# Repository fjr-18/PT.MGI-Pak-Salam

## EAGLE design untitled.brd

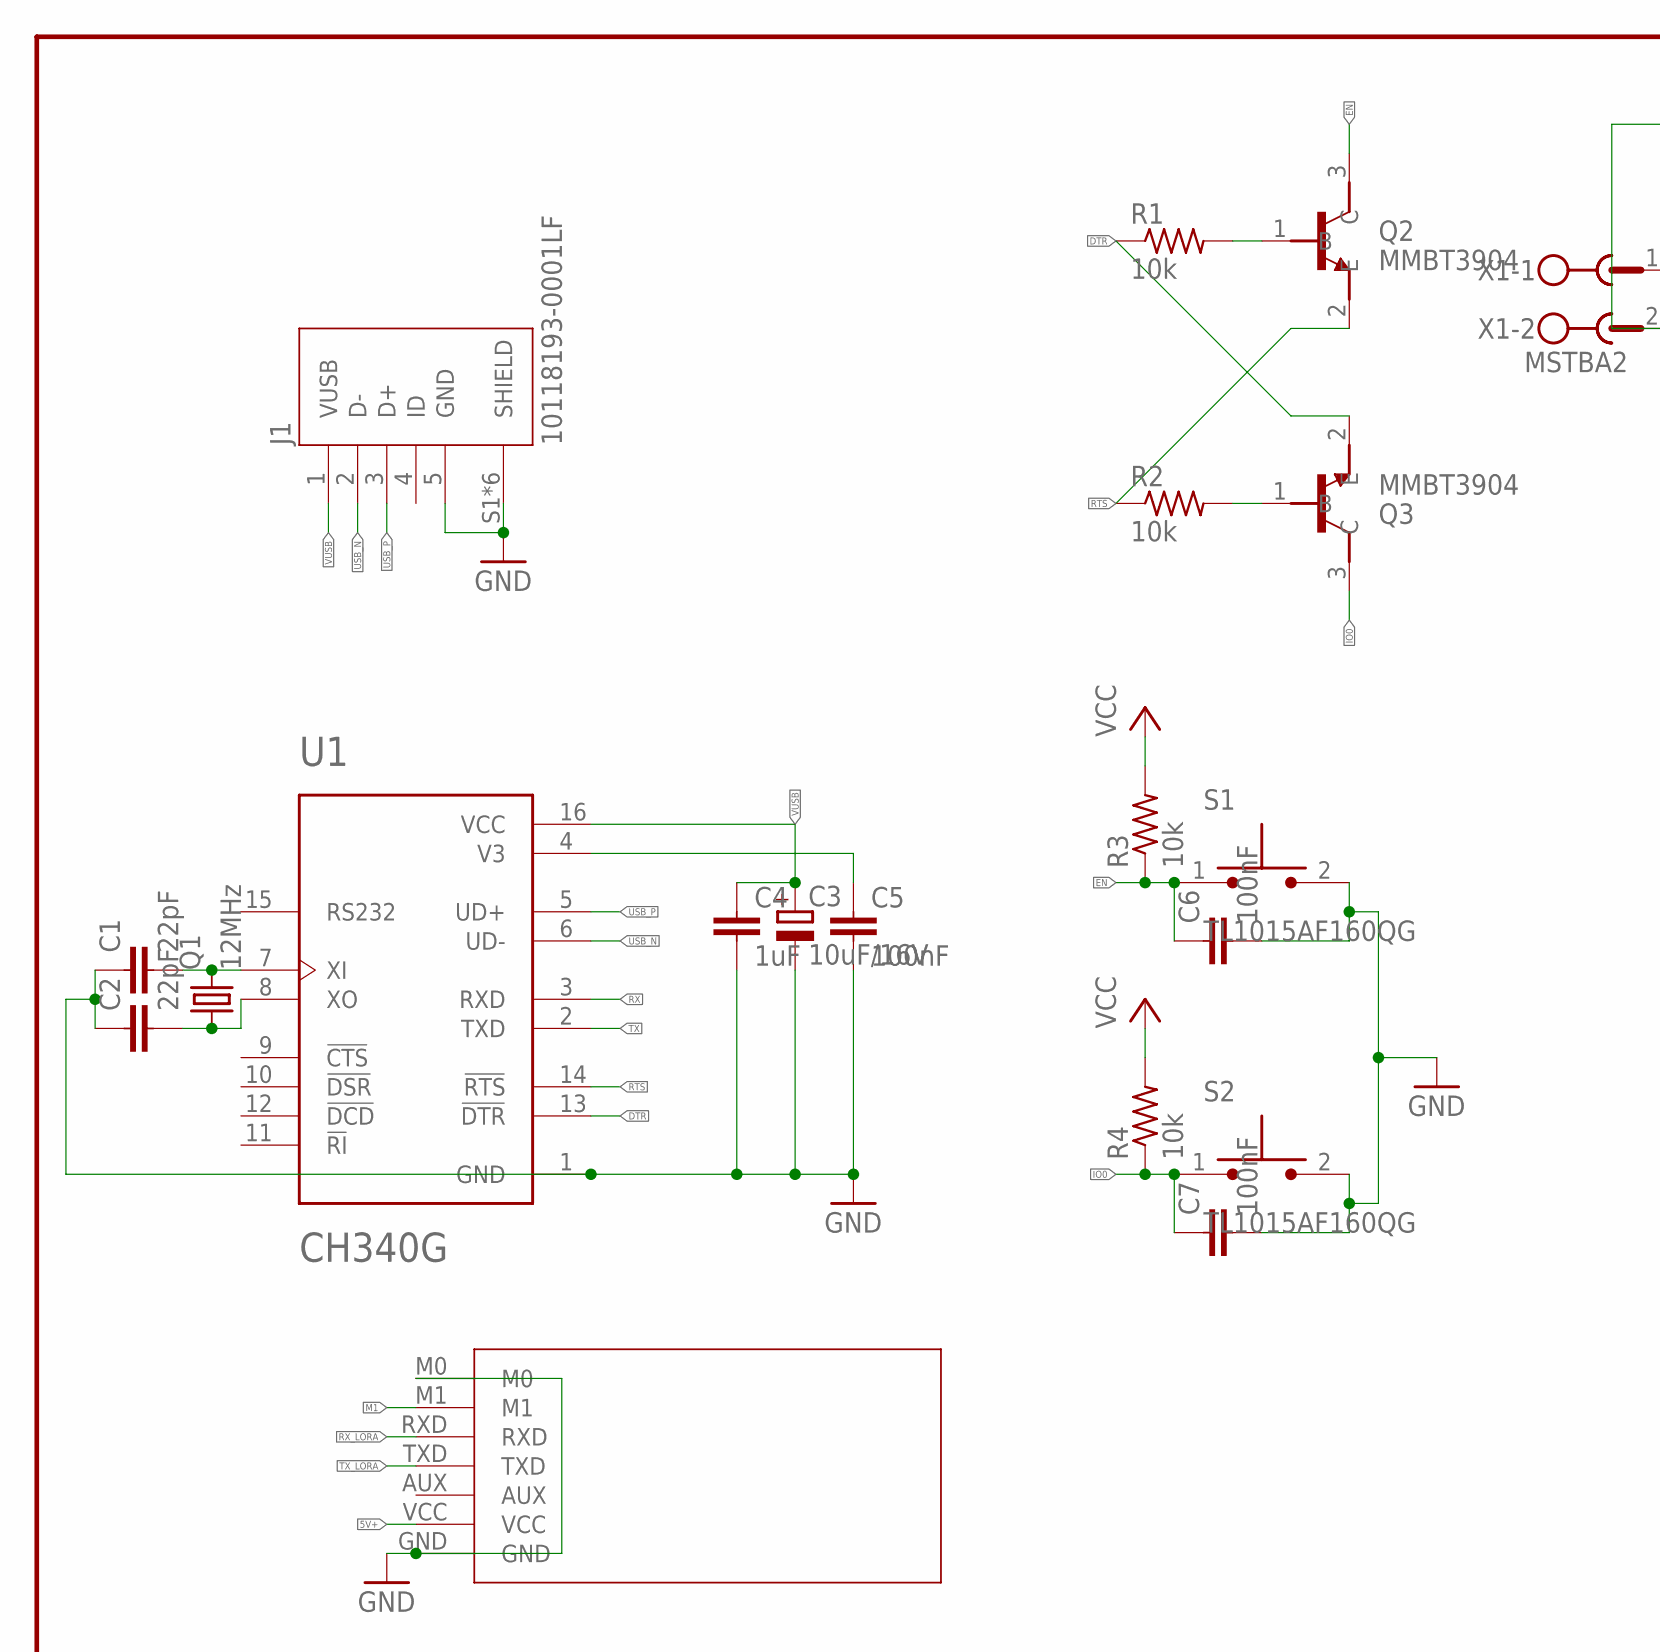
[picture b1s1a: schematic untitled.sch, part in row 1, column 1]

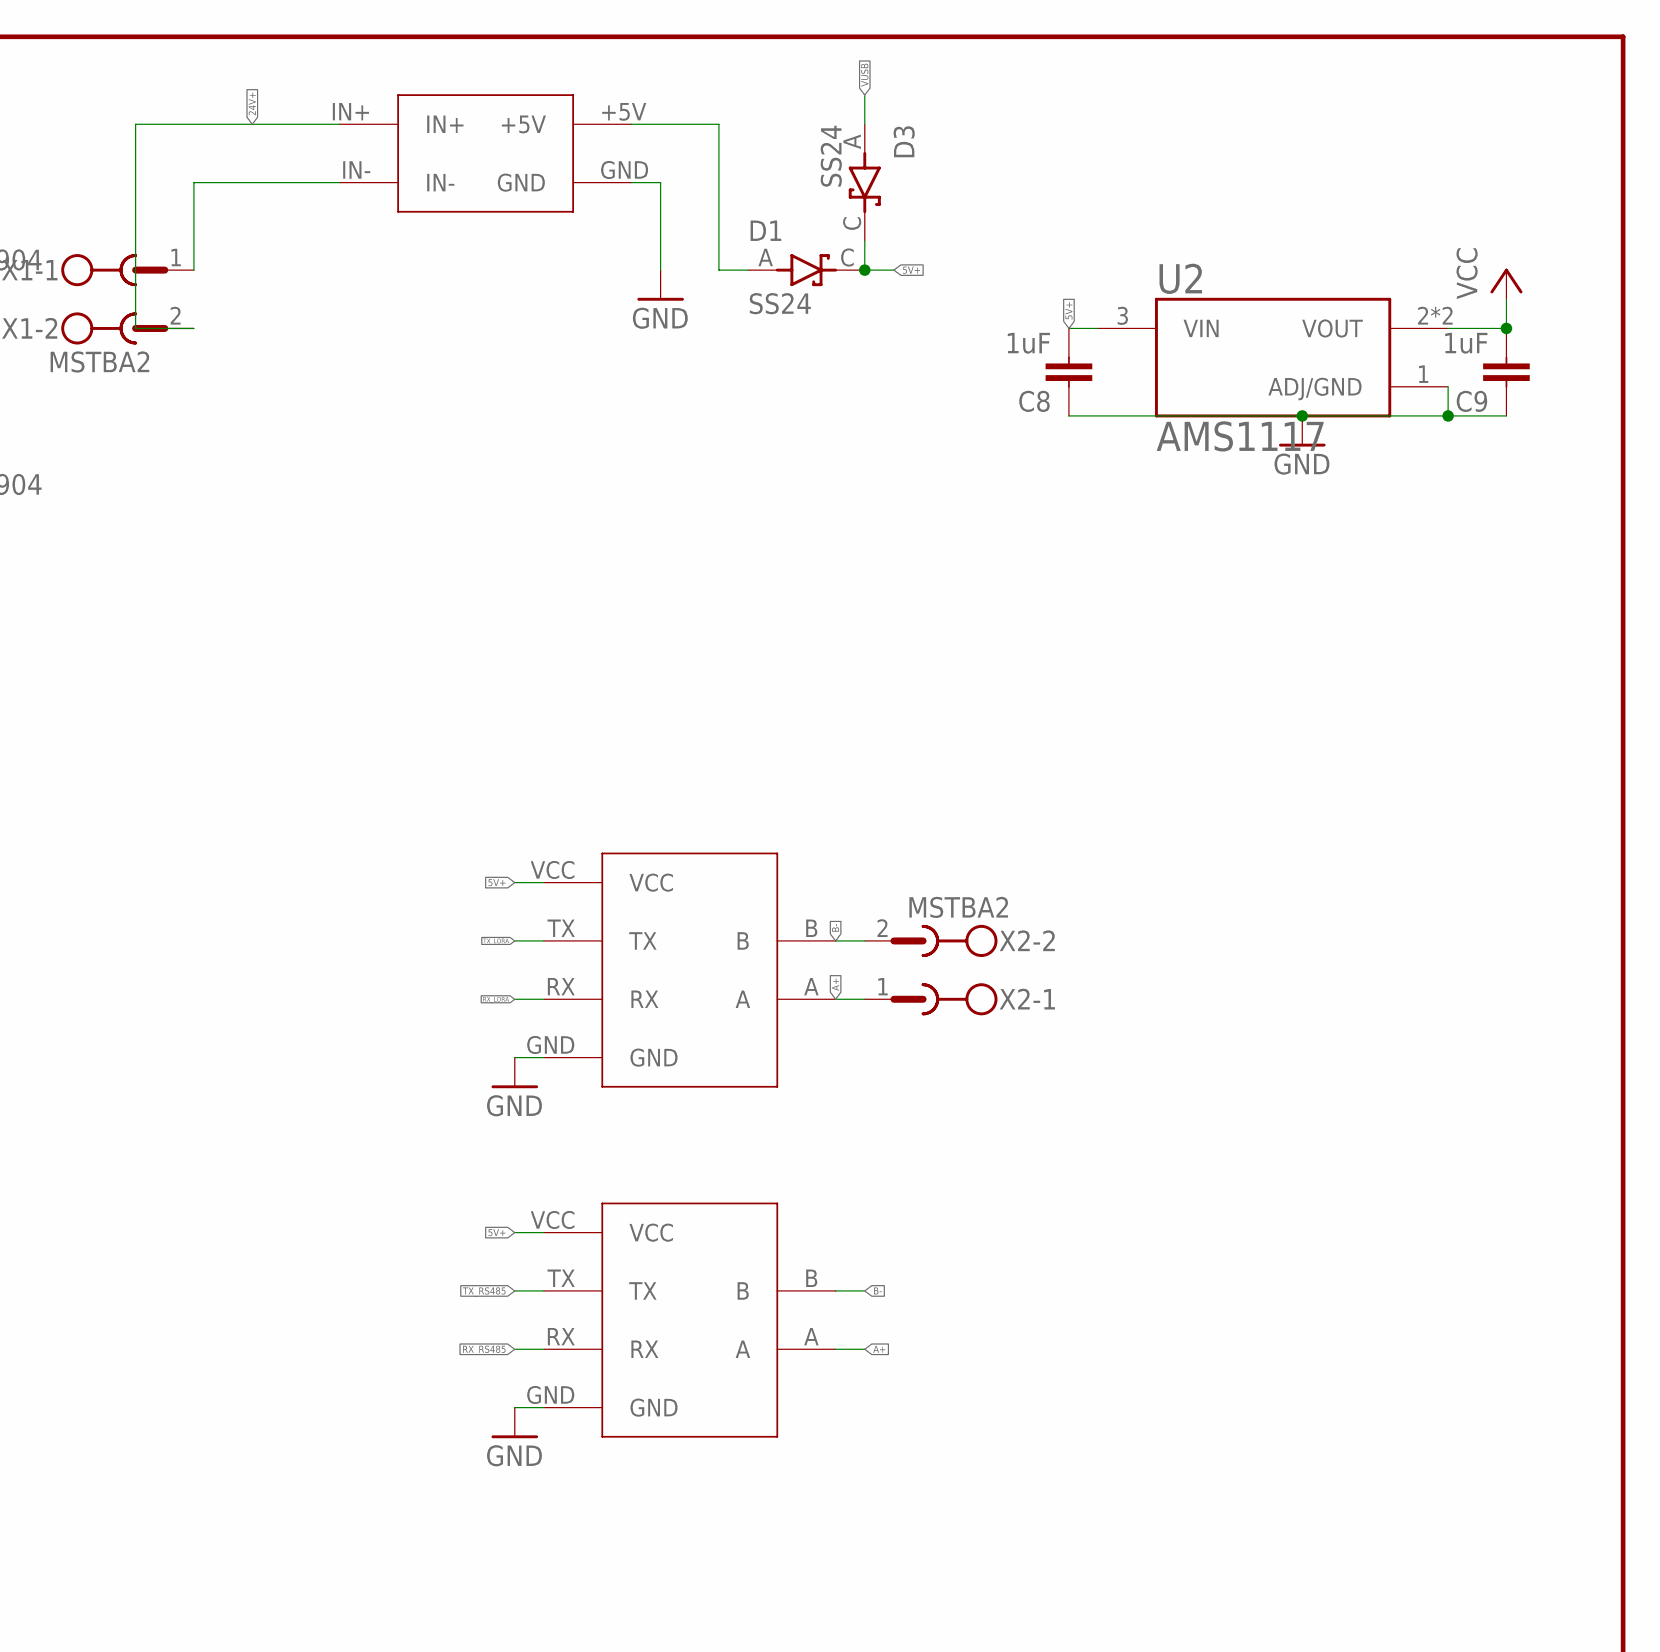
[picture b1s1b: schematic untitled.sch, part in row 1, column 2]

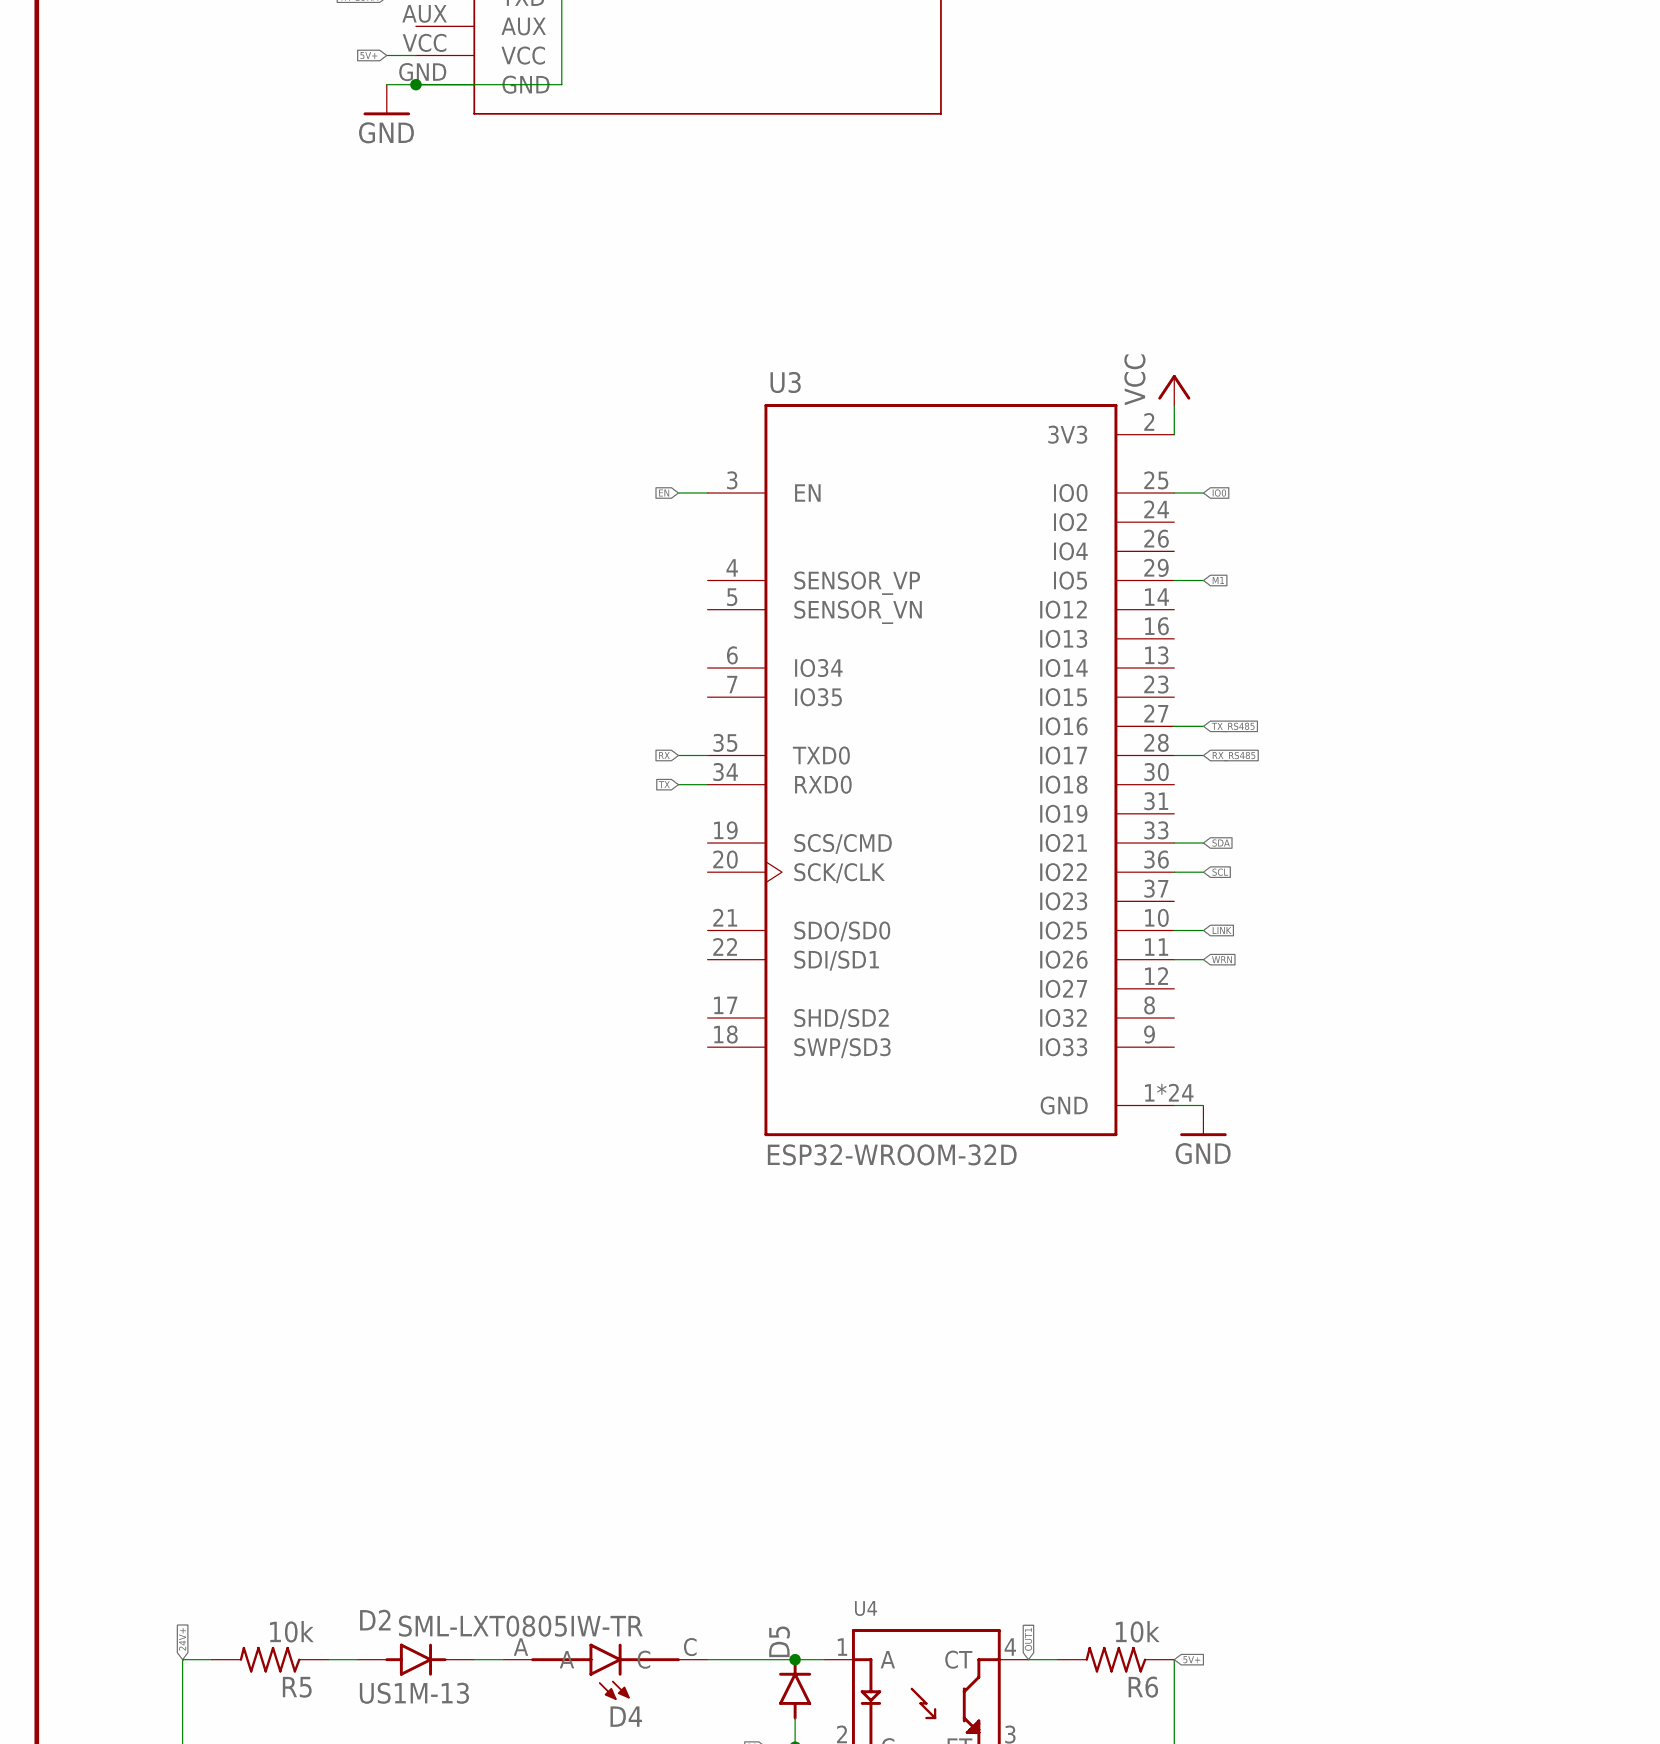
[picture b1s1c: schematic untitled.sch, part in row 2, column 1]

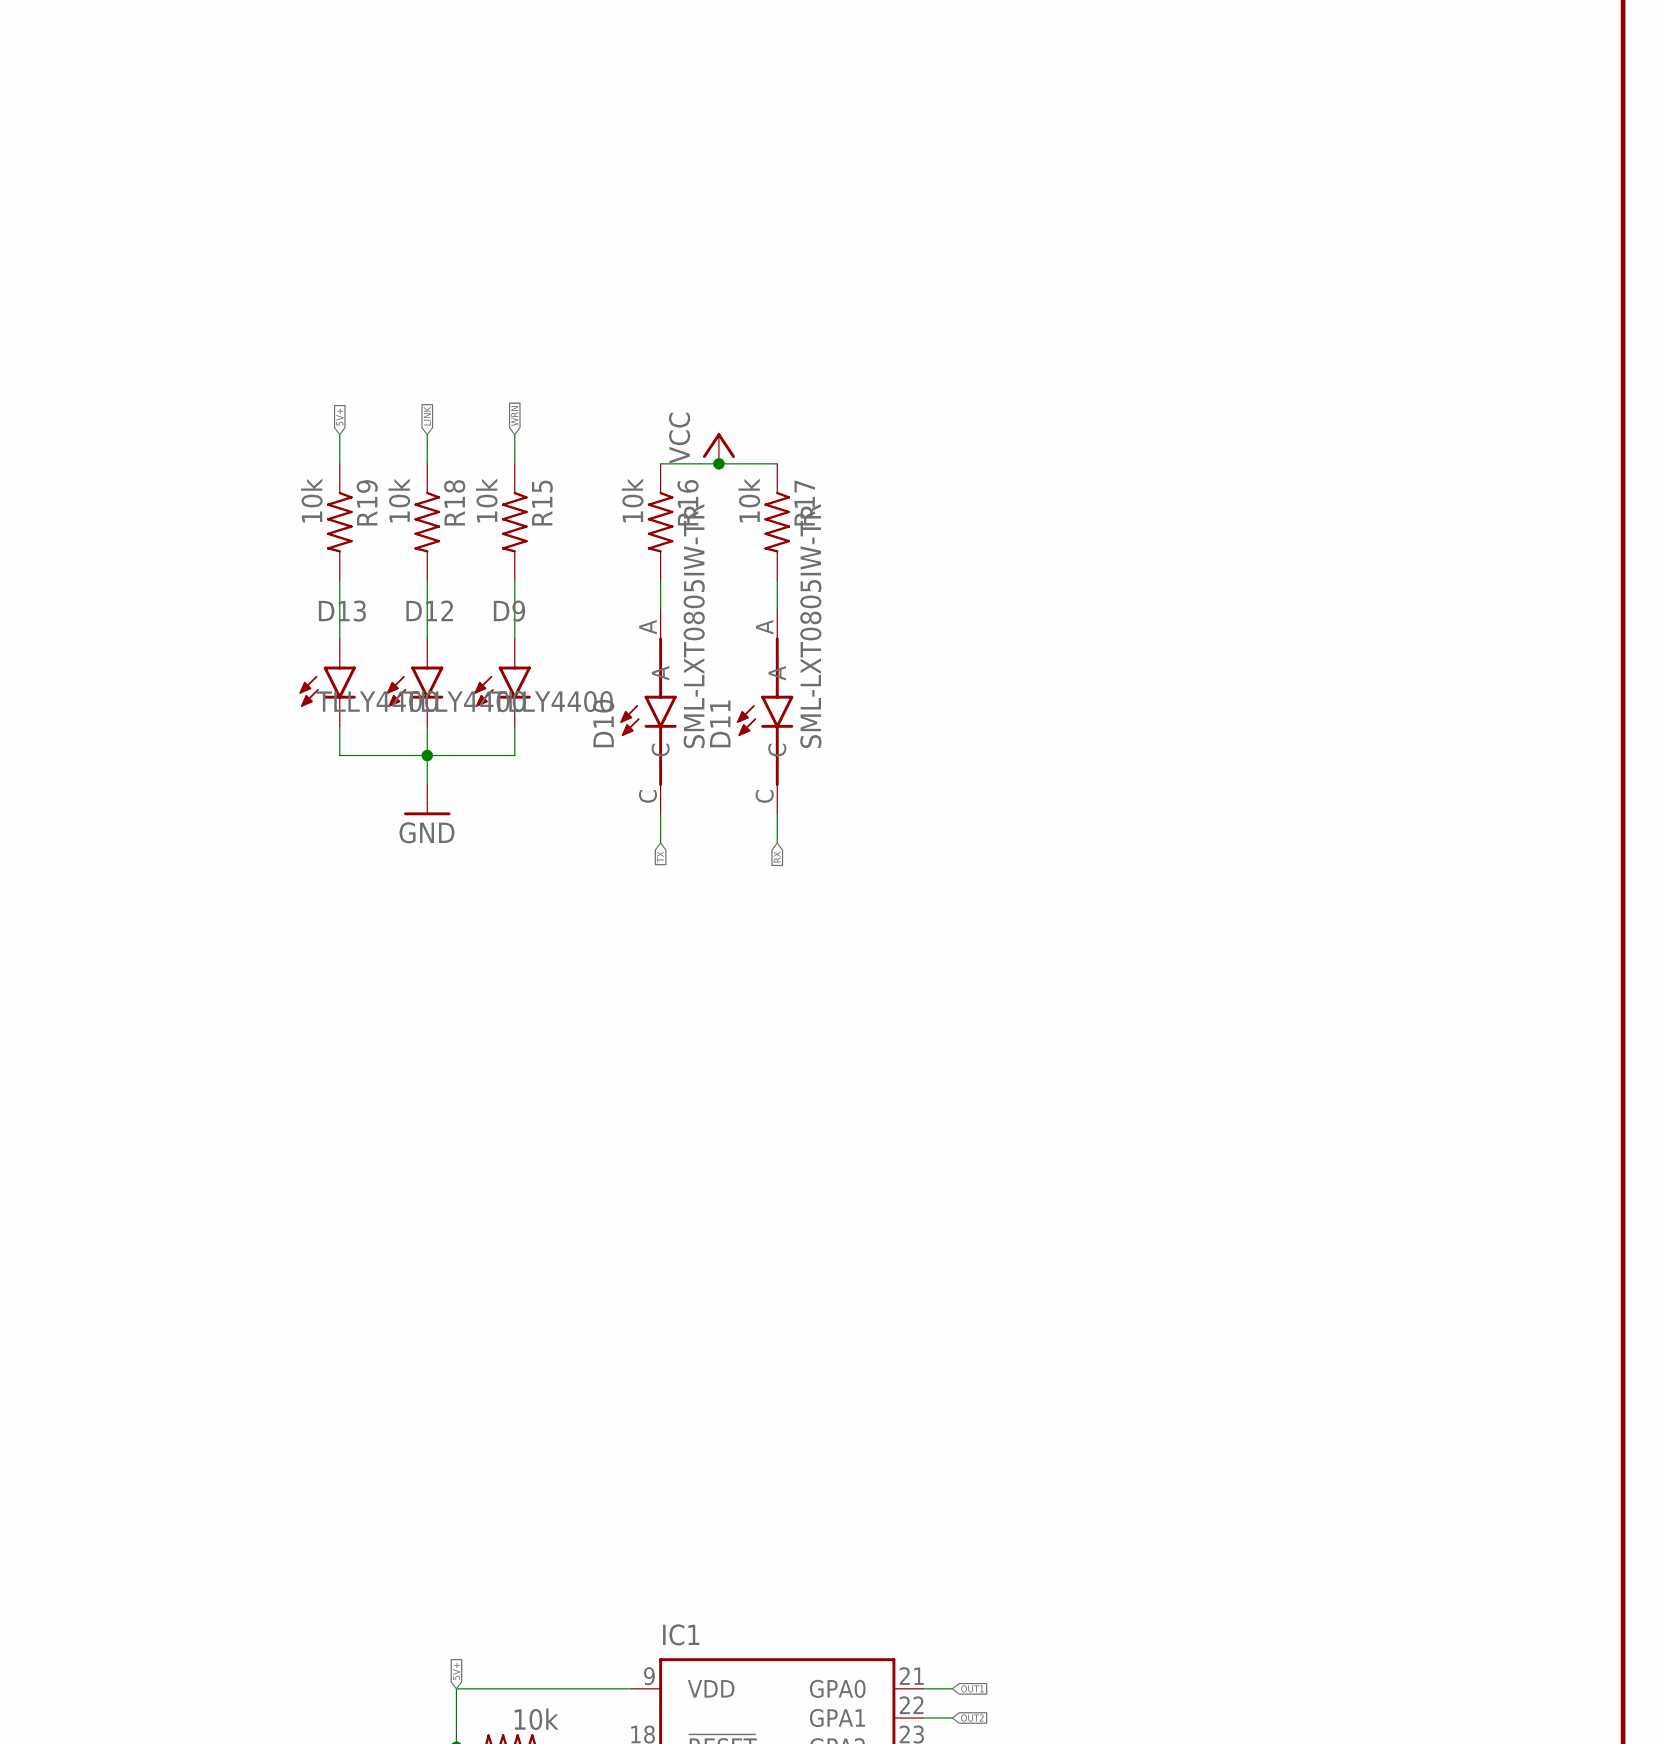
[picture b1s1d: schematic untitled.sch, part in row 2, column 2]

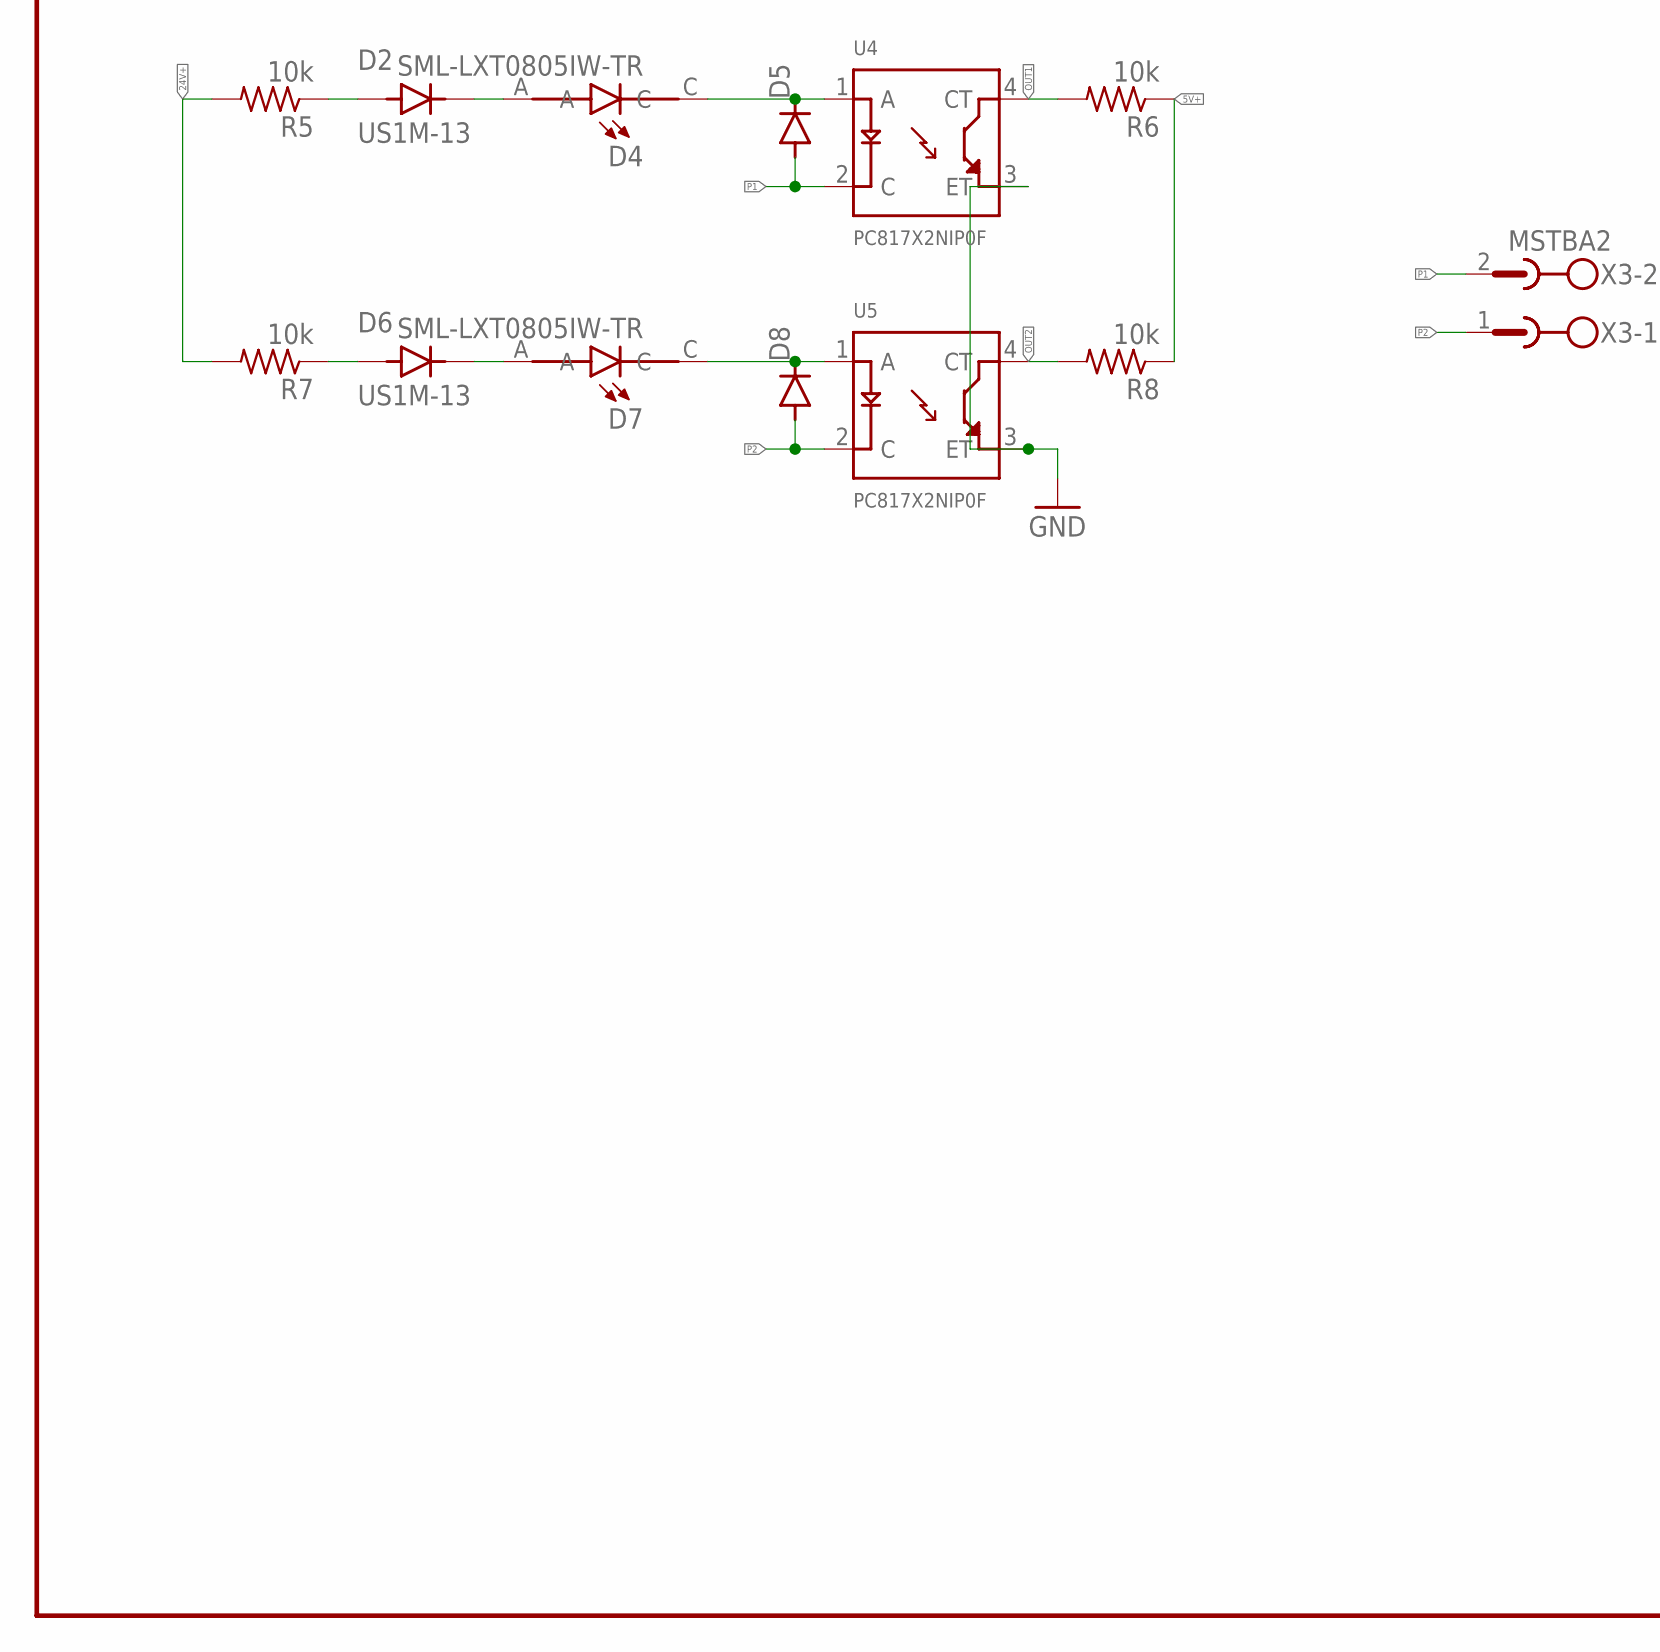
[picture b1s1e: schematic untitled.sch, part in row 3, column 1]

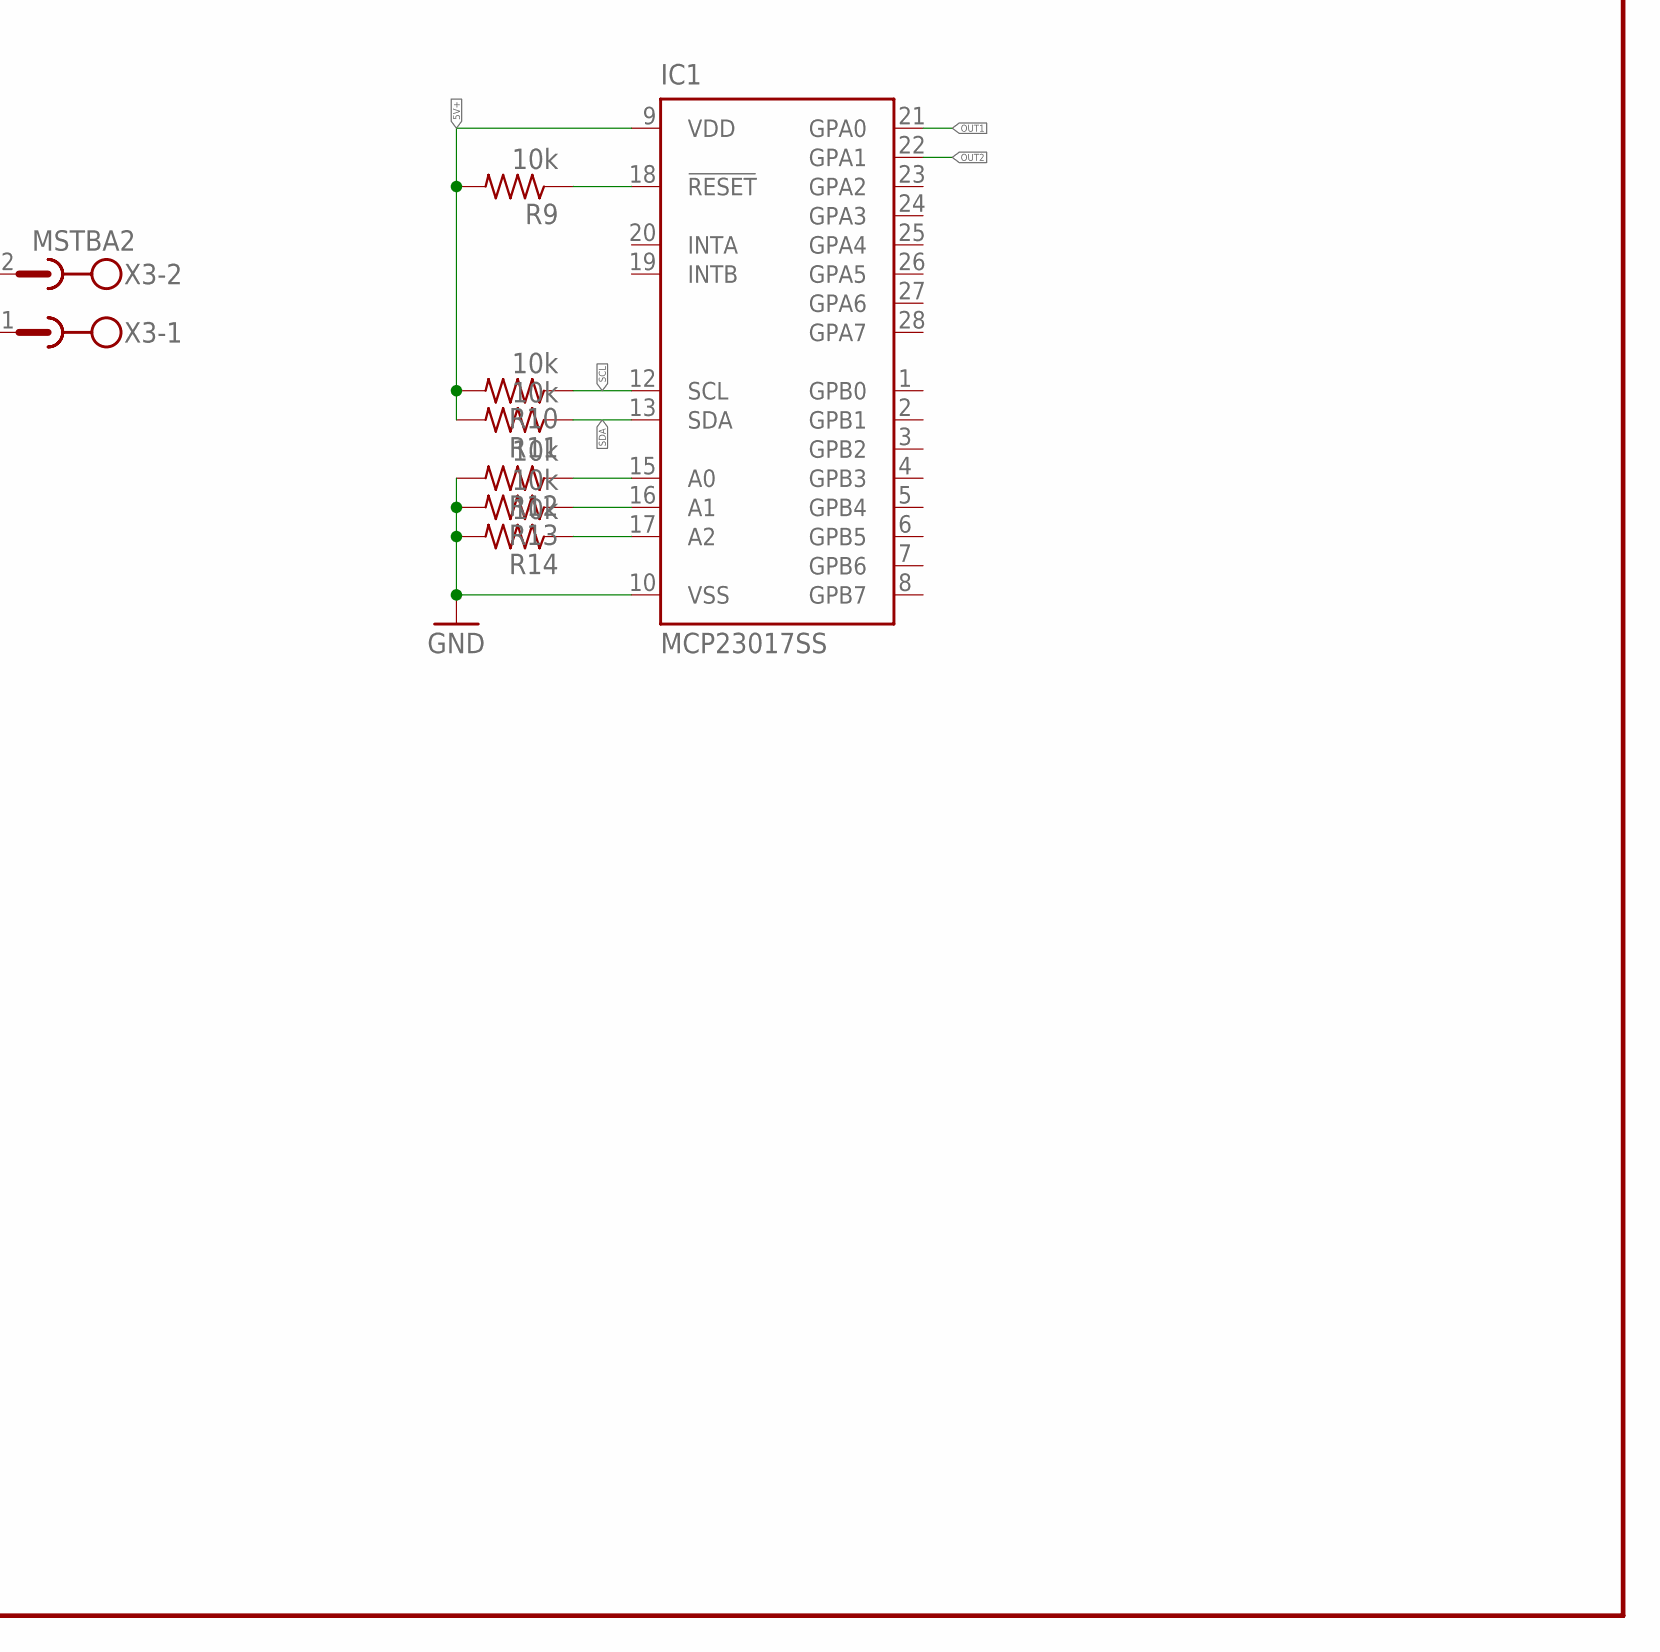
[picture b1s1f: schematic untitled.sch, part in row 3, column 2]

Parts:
C1, C2: 22pF; C0805K
C3: 10uF/16V; 153CLV-0505
C4, C8, C9: 1uF; C0805K
C5, C6, C7: 100nF; C0805K
D1, D3: SS24; DIOM5336X265N
D2, D6: US1M-13; DIOM5226X240N
D4, D7, D10, D11: SML-LXT0805IW-TR; LEDC2012X120N
D5, D8: DIODE-SOD123; SOD123
D9, D12, D13: TLLY4400; LED3MM
EBYTEE220-900T22D1: EBYTEE220-900T22D
IC1: MCP23017SS; SSOP28
J1: 10118193-0001LF; FCI_10118193-0001LF
Q1: 12MHz; SM49
Q2, Q3: MMBT3904; SOT95P240X120-3N
R1, R2, R3, R4, R6, R8, R9, R10, R11, R12, R13, R14, R15, R16, R17, R18, R19: 10k; M0805
R5, R7: 10k; 0207/12
S1, S2: TL1015AF160QG; SW_TL1015AF160QG
SUPER-STEPDOWN1: SUPER-STEPDOWN
TTL-RS1, TTL-RS2: TTL-RS485
U1: CH340G; SOIC127P600X180-16N
U2: AMS1117; SOT229P700X180-4N
U3: ESP32-WROOM-32D; MODULE_ESP32-WROOM-32D
U4, U5: PC817X2NIP0F; SOT254P975X400-4N
X1, X2, X3: MSTBA2

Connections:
5V+: C8.2, D1.C (K), D3.C (K), EBYTEE220-900T22D1.VCC, IC1.9 (VDD), R6.1, R8.1, R9.2, R10.2, R11.2, R19.1, TTL-RS1.VCC, TTL-RS2.VCC, U2.3 (VIN)
24V+: R5.2, R7.2, SUPER-STEPDOWN1.IN+, X1.2
A+: TTL-RS1.A, TTL-RS2.A, X2.1
B-: TTL-RS1.B, TTL-RS2.B, X2.2
DTR: Q3.2 (E), R1.1, U1.13 (!DTR)
EN: C6.1, Q2.3 (C), R3.1, S1.1, U3.3 (EN)
GND: C1.1, C2.1, C3.-, C4.2, C5.2, C6.2, C7.2, C8.1, C9.1, D9.K (C), D12.K (C), D13.K (C), EBYTEE220-900T22D1.GND, EBYTEE220-900T22D1.M0, IC1.10 (VSS), J1.5 (GND), J1.S1 (SHIELD), J1.S2 (SHIELD), J1.S3 (SHIELD), J1.S4 (SHIELD), J1.S5 (SHIELD), J1.S6 (SHIELD), R12.2, R13.2, R14.2, S1.2, S2.2, SUPER-STEPDOWN1.GND, TTL-RS1.GND, TTL-RS2.GND, U1.1 (GND), U2.1 (ADJ/GND), U3.1 (GND), U3.15 (GND), U3.38 (GND), U3.39_1 (GND), U3.39_2 (GND), U3.39_3 (GND), U3.39_4 (GND), U3.39_5 (GND), U3.39_6 (GND), U3.39_7 (GND), U3.39_8 (GND), U3.39_9 (GND), U3.39_10 (GND), U3.39_11 (GND), U3.39_12 (GND), U3.39_13 (GND), U3.39_14 (GND), U3.39_15 (GND), U3.39_16 (GND), U3.39_17 (GND), U3.39_18 (GND), U3.39_19 (GND), U3.39_20 (GND), U3.39_21 (GND), U4.3 (ET), U5.3 (ET)
IO0: C7.1, Q3.3 (C), R4.1, S2.1, U3.25 (IO0)
LINK: R18.1, U3.10 (IO25)
M1: EBYTEE220-900T22D1.M1, U3.29 (IO5)
unnamed: SUPER-STEPDOWN1.IN-, X1.1
unnamed: C5.1, U1.4 (V3)
unnamed: Q2.1 (B), R1.2
unnamed: C1.2, Q1.2, U1.7 (XI)
unnamed: C2.2, Q1.1, U1.8 (XO)
unnamed: Q3.1 (B), R2.2
unnamed: D10.A, R16.2
unnamed: D1.A, SUPER-STEPDOWN1.+5V
unnamed: D2.A, R5.1
unnamed: D2.C (K), D4.A
unnamed: D4.C, D5.C, U4.1 (A)
unnamed: IC1.15 (A0), R12.1
unnamed: IC1.16 (A1), R13.1
unnamed: IC1.17 (A2), R14.1
unnamed: D6.A, R7.1
unnamed: D6.C (K), D7.A
unnamed: D7.C, D8.C, U5.1 (A)
unnamed: D11.A, R17.2
unnamed: D13.A, R19.2
unnamed: IC1.18 (!RESET), R9.1
unnamed: D12.A, R18.2
unnamed: D9.A, R15.2
OUT1: IC1.21 (GPA0), R6.2, U4.4 (CT)
OUT2: IC1.22 (GPA1), R8.2, U5.4 (CT)
P1: D5.A, U4.2 (C), X3.2
P2: D8.A, U5.2 (C), X3.1
RTS: Q2.2 (E), R2.1, U1.14 (!RTS)
RX: D11.C, U1.3 (RXD), U3.35 (TXD0)
RX_LORA: EBYTEE220-900T22D1.RXD, TTL-RS1.RX
RX_RS485: TTL-RS2.RX, U3.28 (IO17)
SCL: IC1.12 (SCL), R10.1, U3.36 (IO22)
SDA: IC1.13 (SDA), R11.1, U3.33 (IO21)
TX: D10.C, U1.2 (TXD), U3.34 (RXD0)
TX_LORA: EBYTEE220-900T22D1.TXD, TTL-RS1.TX
TX_RS485: TTL-RS2.TX, U3.27 (IO16)
USB_N: J1.2 (D-), U1.6 (UD-)
USB_P: J1.3 (D+), U1.5 (UD+)
VCC: C9.2, R3.2, R4.2, R16.1, R17.1, U2.2 (VOUT), U2.4 (VOUT), U3.2 (3V3)
VUSB: C3.+, C4.1, D3.A, J1.1 (VUSB), U1.16 (VCC)
WRN: R15.1, U3.11 (IO26)

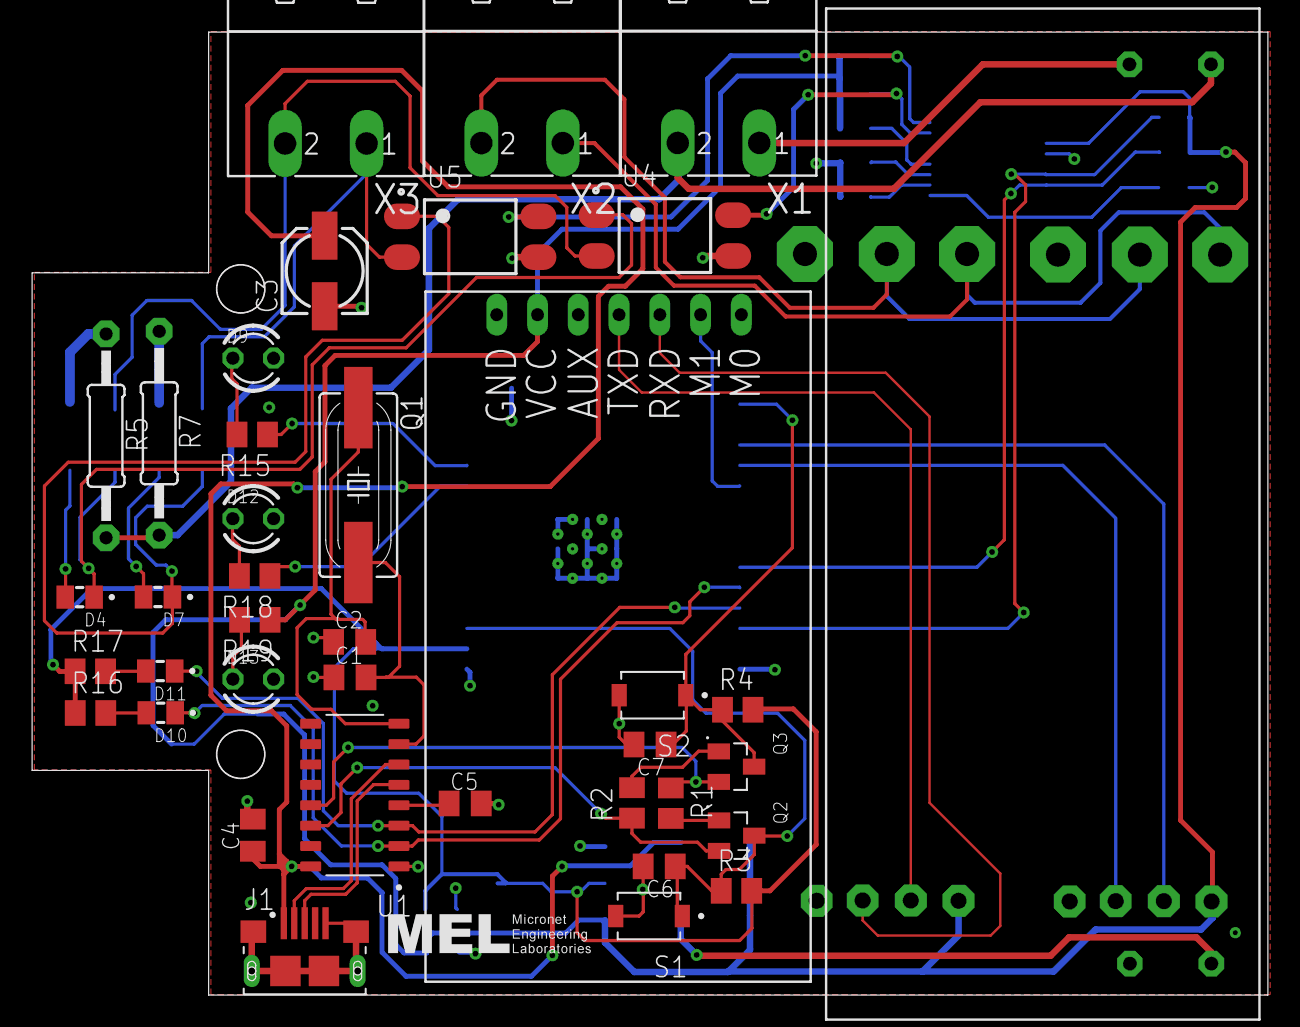
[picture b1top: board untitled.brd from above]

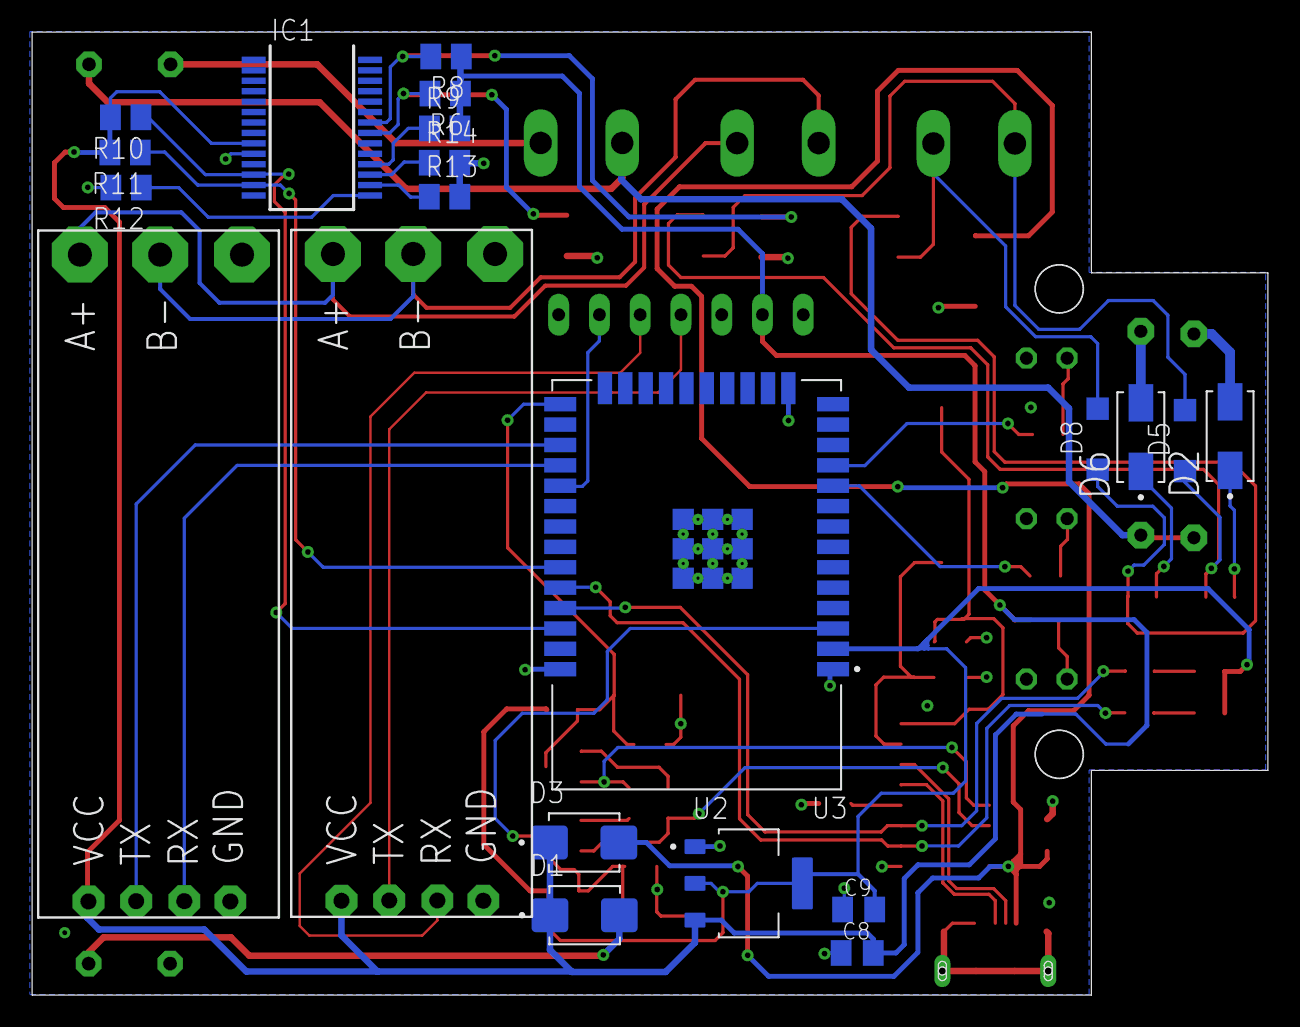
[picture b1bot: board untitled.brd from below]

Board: 2 copper layers, 77.0 x 60.0 mm, 60 parts (21 on the bottom side), 50 nets.

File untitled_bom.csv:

Comment,Designator,Footprint,LCSC Part #
,EBYTEE220-900T22D1,EBYTEE220-900T22D,
,D5,SOD123,
,D8,SOD123,
,SUPER-STEPDOWN1,SUPER-STEPDOWN,
,TTL-RS1,TTL-RS485,
,TTL-RS2,TTL-RS485,
1uF,C4 C8 C9,C0805K,
10k,R5 R7,0207/12,
10k,R1 R2 R3 R4 R6 R8 R9 R10 R11 R12 R13 R14 R15 R16 R17 R18 R19,M0805,
10uF/16V,C3,153CLV-0505,
12MHz,Q1,SM49,
22pF,C1 C2,C0805K,
100nF,C5 C6 C7,C0805K,
10118193-0001LF,J1,FCI_10118193-0001LF,
AMS1117,U2,SOT229P700X180-4N,
CH340G,U1,SOIC127P600X180-16N,
ESP32-WROOM-32D,U3,MODULE_ESP32-WROOM-32D,
MCP23017SS,IC1,SSOP28,
MMBT3904,Q2 Q3,SOT95P240X120-3N,
MSTBA2,X1 X2 X3,MSTBA2,
PC817X2NIP0F,U4 U5,SOT254P975X400-4N,
SML-LXT0805IW-TR,D4 D7 D10 D11,LEDC2012X120N,
SS24,D1 D3,DIOM5336X265N,
TL1015AF160QG,S1 S2,SW_TL1015AF160QG,
TLLY4400,D9 D12 D13,LED3MM,
US1M-13,D2 D6,DIOM5226X240N,
